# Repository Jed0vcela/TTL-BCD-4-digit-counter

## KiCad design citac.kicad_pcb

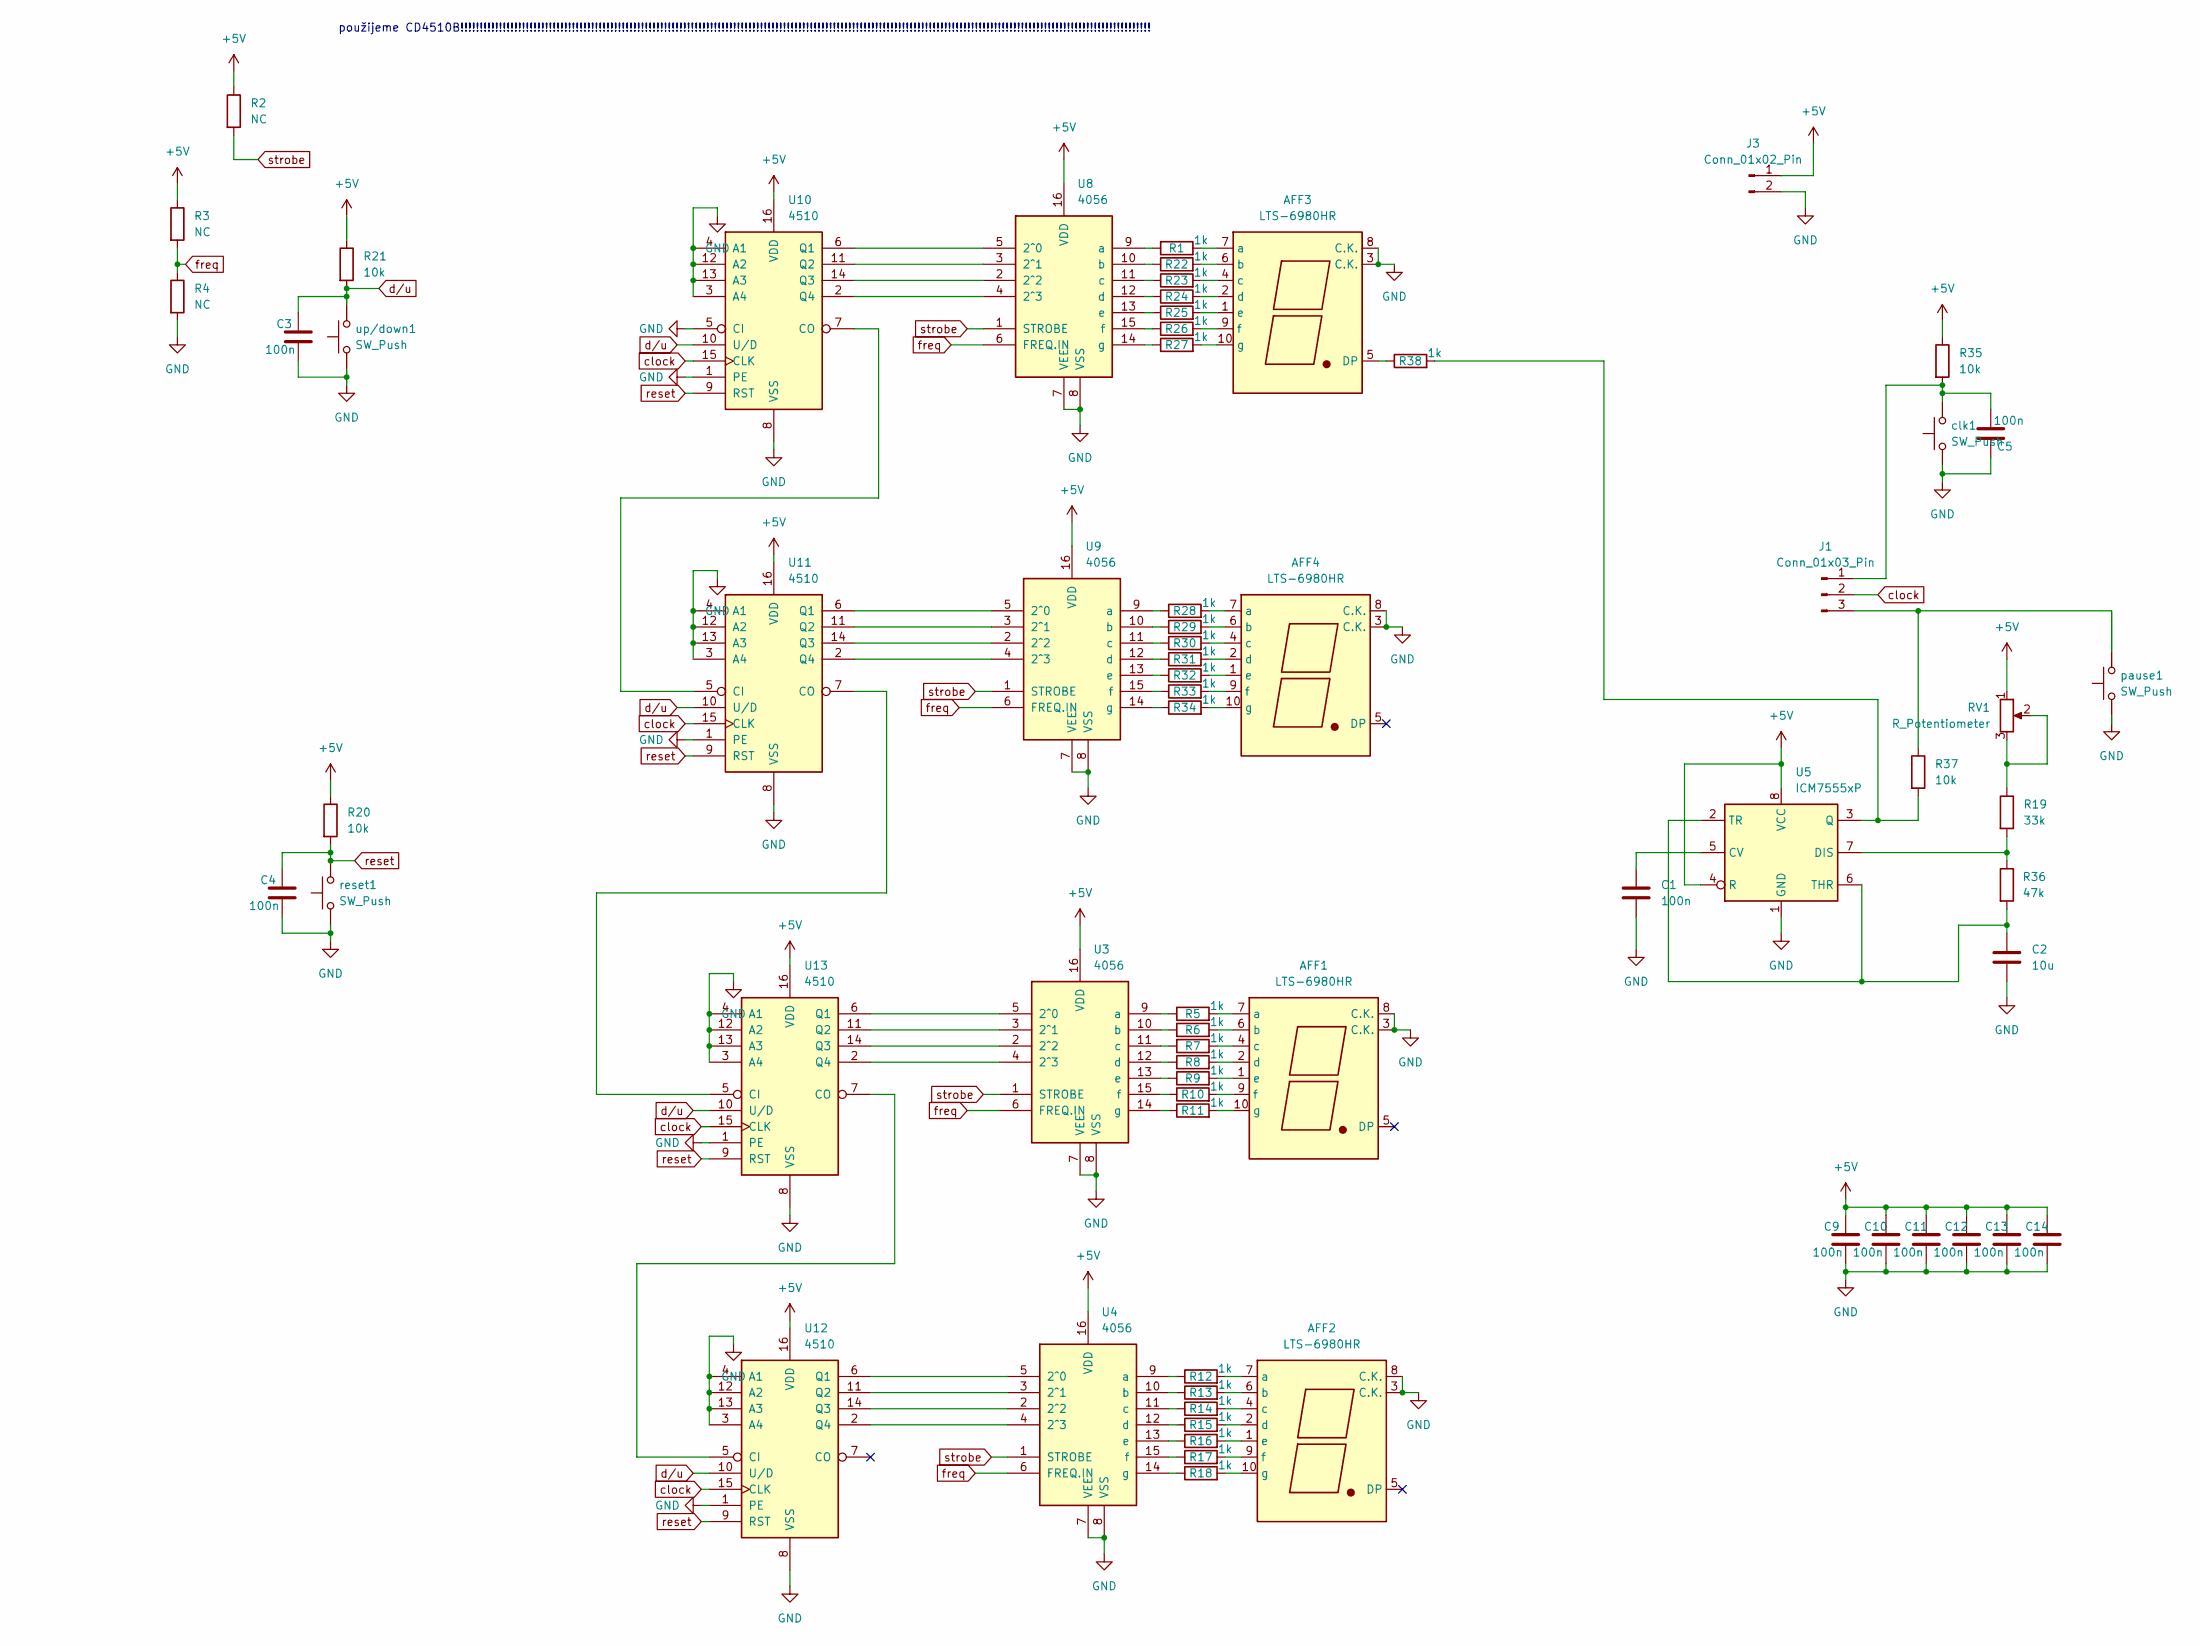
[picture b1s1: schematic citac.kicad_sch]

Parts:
AFF1, AFF2, AFF3, AFF4: LTS-6980HR; 7SegmentLED_LTS6760_LTS6780
C1, C3, C4, C5, C9, C10, C11, C12, C13, C14: 100n; C_1206_3216Metric
C2: 10u; C_1206_3216Metric
J1: Conn_01x03_Pin; PinHeader_1x03_P2.54mm_Vertical
J3: Conn_01x02_Pin; JST_EH_S2B-EH_1x02_P2.50mm_Horizontal
R1, R5, R6, R7, R8, R9, R10, R11, R12, R13, R14, R15, R16, R17, R18, R22, R23, R24, R25, R26, R27, R28, R29, R30, R31, R32, R33, R34, R38: 1k; R_Axial_DIN0207_L6.3mm_D2.5mm_P10.16mm_Horizontal
R2, R3, R4: NC; R_Axial_DIN0207_L6.3mm_D2.5mm_P10.16mm_Horizontal
R19: 33k; R_Axial_DIN0207_L6.3mm_D2.5mm_P10.16mm_Horizontal
R20, R21, R35, R37: 10k; R_Axial_DIN0207_L6.3mm_D2.5mm_P10.16mm_Horizontal
R36: 47k; R_Axial_DIN0207_L6.3mm_D2.5mm_P10.16mm_Horizontal
RV1: R_Potentiometer; Potentiometer_ACP_CA9-V10_Vertical_Hole
U3, U4, U8, U9: 4056; DIP-16_W7.62mm
U5: ICM7555xP; DIP-8_W7.62mm_Socket_LongPads
U10, U11, U12, U13: 4510; DIP-16_W7.62mm_LongPads
clk1: SW_Push; SW_PUSH_6mm
pause1: SW_Push; SW_PUSH_6mm
reset1: SW_Push; SW_PUSH_6mm
up/down1: SW_Push; SW_PUSH_6mm

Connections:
+5V: C9.1, C10.1, C11.1, C12.1, C13.1, C14.1, J3.1, R2.1, R3.1, R20.1, R21.1, R35.1, RV1.1, U3.16 (VDD), U4.16 (VDD), U5.4 (R), U5.8 (VCC), U8.16 (VDD), U9.16 (VDD), U10.16 (VDD), U11.16 (VDD), U12.16 (VDD), U13.16 (VDD)
GND: AFF1.3 (C.K.), AFF1.8 (C.K.), AFF2.3 (C.K.), AFF2.8 (C.K.), AFF3.3 (C.K.), AFF3.8 (C.K.), AFF4.3 (C.K.), AFF4.8 (C.K.), C1.2, C2.2, C3.2, C4.2, C5.1, C9.2, C10.2, C11.2, C12.2, C13.2, C14.2, J3.2, R4.2, U3.7 (VEE), U3.8 (VSS), U4.7 (VEE), U4.8 (VSS), U5.1 (GND), U8.7 (VEE), U8.8 (VSS), U9.7 (VEE), U9.8 (VSS), U10.1 (PE), U10.3 (A4), U10.4 (A1), U10.5 (CI), U10.8 (VSS), U10.12 (A2), U10.13 (A3), U11.1 (PE), U11.3 (A4), U11.4 (A1), U11.8 (VSS), U11.12 (A2), U11.13 (A3), U12.1 (PE), U12.3 (A4), U12.4 (A1), U12.8 (VSS), U12.12 (A2), U12.13 (A3), U13.1 (PE), U13.3 (A4), U13.4 (A1), U13.8 (VSS), U13.12 (A2), U13.13 (A3), clk1.1, pause1.1, reset1.1, up/down1.1
unnamed: AFF1.7 (a), R5.2
unnamed: AFF1.6 (b), R6.2
unnamed: AFF1.4 (c), R7.2
unnamed: AFF1.2 (d), R8.2
unnamed: AFF1.1 (e), R9.2
unnamed: AFF1.9 (f), R10.2
unnamed: AFF1.10 (g), R11.2
unnamed: AFF2.7 (a), R12.2
unnamed: AFF2.6 (b), R13.2
unnamed: AFF2.4 (c), R14.2
unnamed: AFF2.2 (d), R15.2
unnamed: AFF2.1 (e), R16.2
unnamed: AFF2.9 (f), R17.2
unnamed: AFF2.10 (g), R18.2
unnamed: AFF3.5 (DP), R38.1
unnamed: AFF3.7 (a), R1.2
unnamed: AFF3.6 (b), R22.2
unnamed: AFF3.4 (c), R23.2
unnamed: AFF3.2 (d), R24.2
unnamed: AFF3.1 (e), R25.2
unnamed: AFF3.9 (f), R26.2
unnamed: AFF3.10 (g), R27.2
unnamed: AFF4.7 (a), R28.2
unnamed: AFF4.6 (b), R29.2
unnamed: AFF4.4 (c), R30.2
unnamed: AFF4.2 (d), R31.2
unnamed: AFF4.1 (e), R32.2
unnamed: AFF4.9 (f), R33.2
unnamed: AFF4.10 (g), R34.2
unnamed: C5.2, J1.1, R35.2, clk1.2
unnamed: J1.3, R37.1, pause1.2
unnamed: R19.1, RV1.2, RV1.3
unnamed: R5.1, U3.9 (a)
unnamed: R6.1, U3.10 (b)
unnamed: R7.1, U3.11 (c)
unnamed: R8.1, U3.12 (d)
unnamed: R9.1, U3.13 (e)
unnamed: R10.1, U3.15 (f)
unnamed: R11.1, U3.14 (g)
unnamed: R12.1, U4.9 (a)
unnamed: R13.1, U4.10 (b)
unnamed: R14.1, U4.11 (c)
unnamed: R15.1, U4.12 (d)
unnamed: R16.1, U4.13 (e)
unnamed: R17.1, U4.15 (f)
unnamed: R18.1, U4.14 (g)
unnamed: C1.1, U5.5 (CV)
unnamed: R19.2, R36.1, U5.7 (DIS)
unnamed: R37.2, R38.2, U5.3 (Q)
unnamed: C2.1, R36.2, U5.2 (TR), U5.6 (THR)
unnamed: R1.1, U8.9 (a)
unnamed: R22.1, U8.10 (b)
unnamed: R23.1, U8.11 (c)
unnamed: R24.1, U8.12 (d)
unnamed: R25.1, U8.13 (e)
unnamed: R26.1, U8.15 (f)
unnamed: R27.1, U8.14 (g)
unnamed: R28.1, U9.9 (a)
unnamed: R29.1, U9.10 (b)
unnamed: R30.1, U9.11 (c)
unnamed: R31.1, U9.12 (d)
unnamed: R32.1, U9.13 (e)
unnamed: R33.1, U9.15 (f)
unnamed: R34.1, U9.14 (g)
unnamed: U10.7 (CO), U11.5 (CI)
unnamed: U8.5 (2^0), U10.6 (Q1)
unnamed: U8.3 (2^1), U10.11 (Q2)
unnamed: U8.2 (2^2), U10.14 (Q3)
unnamed: U8.4 (2^3), U10.2 (Q4)
unnamed: U11.7 (CO), U13.5 (CI)
unnamed: U9.5 (2^0), U11.6 (Q1)
unnamed: U9.3 (2^1), U11.11 (Q2)
unnamed: U9.2 (2^2), U11.14 (Q3)
unnamed: U9.4 (2^3), U11.2 (Q4)
unnamed: U12.5 (CI), U13.7 (CO)
unnamed: U4.5 (2^0), U12.6 (Q1)
unnamed: U4.3 (2^1), U12.11 (Q2)
unnamed: U4.2 (2^2), U12.14 (Q3)
unnamed: U4.4 (2^3), U12.2 (Q4)
unnamed: U3.5 (2^0), U13.6 (Q1)
unnamed: U3.3 (2^1), U13.11 (Q2)
unnamed: U3.2 (2^2), U13.14 (Q3)
unnamed: U3.4 (2^3), U13.2 (Q4)
clock: J1.2, U10.15 (CLK), U11.15 (CLK), U12.15 (CLK), U13.15 (CLK)
d/u: C3.1, R21.2, U10.10 (U/D), U11.10 (U/D), U12.10 (U/D), U13.10 (U/D), up/down1.2
freq: R3.2, R4.1, U3.6 (FREQ.IN), U4.6 (FREQ.IN), U8.6 (FREQ.IN), U9.6 (FREQ.IN)
reset: C4.1, R20.2, U10.9 (RST), U11.9 (RST), U12.9 (RST), U13.9 (RST), reset1.2
strobe: R2.2, U3.1 (STROBE), U4.1 (STROBE), U8.1 (STROBE), U9.1 (STROBE)

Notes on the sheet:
použijeme CD4510B!!!!!!!!!!!!!!!!!!!!!!!!!!!!!!!!!!!!!!!!!!!!!!!!!!!!!!!!!!!!!!!!!!!!!!!!!!!!!!!!!!!!!!!!!!!!!!!!!!!!!!!!!!!!!!!!!!!!!!!!!!!!!!!!!!!!!!!!!!!!!!!!!!!!!!!!!!!!!!!!!!!!!!!!!!!!!!!!!!!!

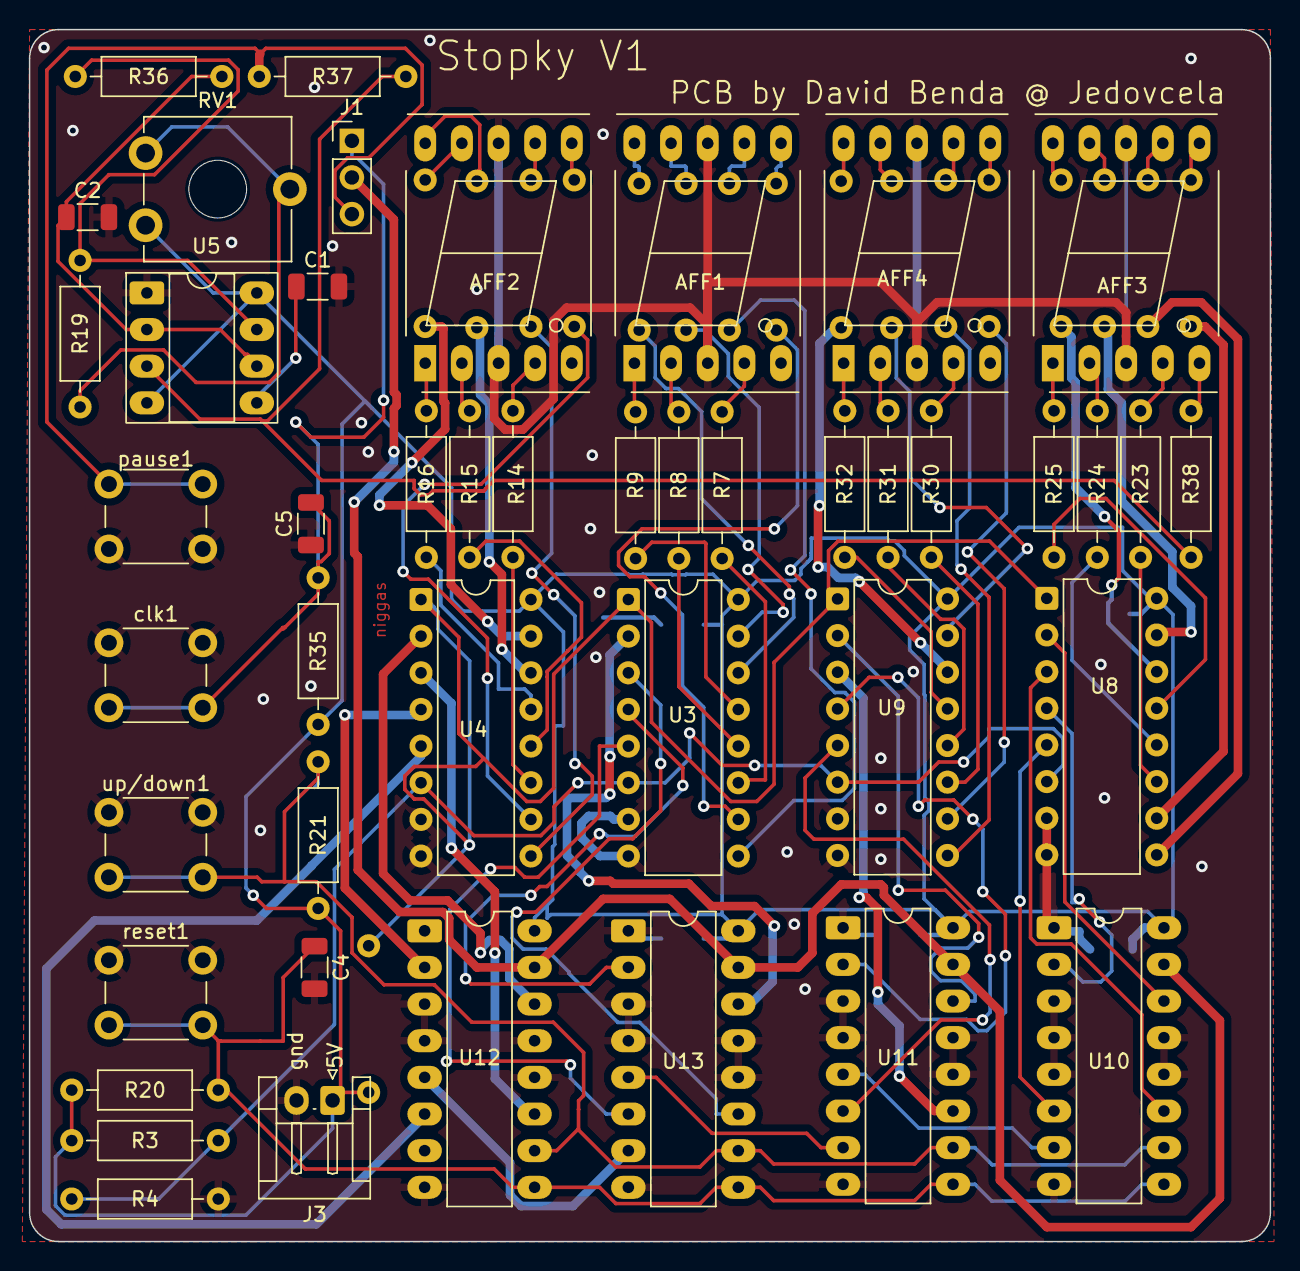
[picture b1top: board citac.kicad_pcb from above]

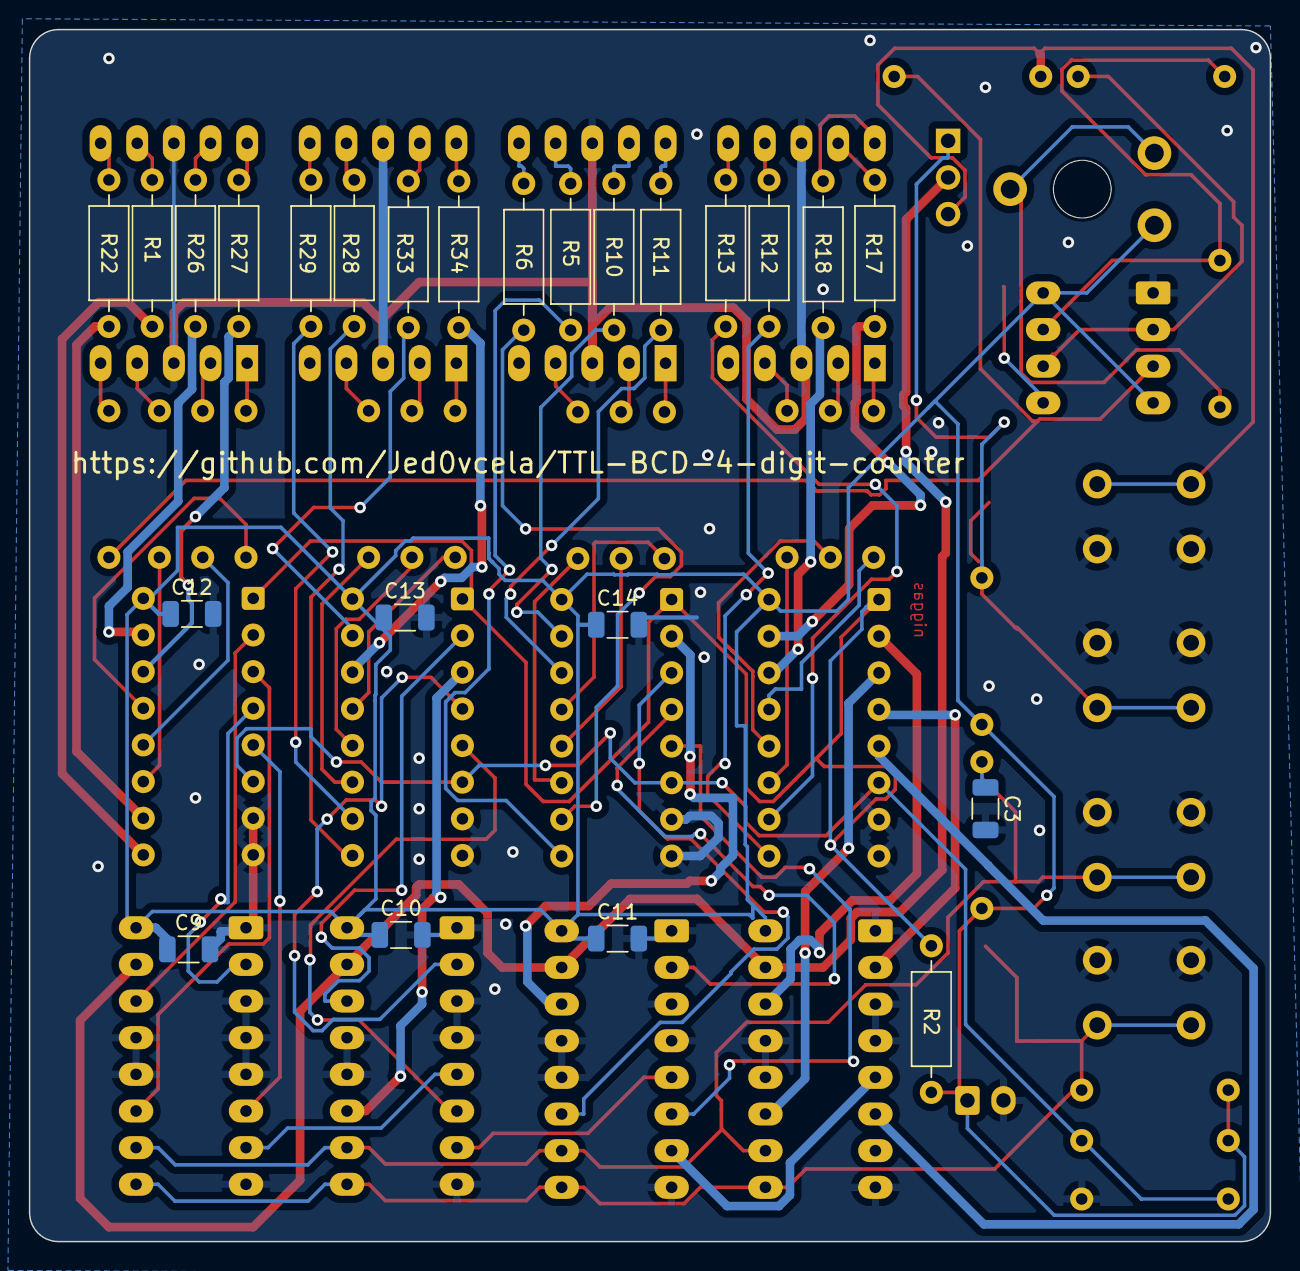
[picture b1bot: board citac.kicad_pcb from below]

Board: 2 copper layers, 86.0 x 84.0 mm, 69 parts (24 on the bottom side), 90 nets.

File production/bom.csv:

Designator,Footprint,Quantity,Value,LCSC Part #
"AFF1, AFF2, AFF3, AFF4",7SegmentLED_LTS6760_LTS6780,4,LTS-6980HR,
"C1, C10, C11, C12, C13, C14, C3, C4, C5, C9",1206,10,100n,
C2,1206,1,10u,
"CLK1, PAUSE1, RESET1, UP/DOWN1",SW_PUSH_6mm,4,SW_Push,
J1,PinHeader_1x03_P2.54mm_Vertical,1,Conn_01x03_Pin,
J3,JST_EH_S2B-EH_1x02_P2.50mm_Horizontal,1,Conn_01x02_Pin,
"R1, R10, R11, R12, R13, R14, R15, R16, R17, R18, R22, R23, R24, R25, R26, R27, R28, R29, R30, R31, R32, R33, R34, R38, R5, R6, R7, R8, R9",R_Axial_DIN0207_L6.3mm_D2.5mm_P10.16mm_Horizontal,29,1k,
R19,R_Axial_DIN0207_L6.3mm_D2.5mm_P10.16mm_Horizontal,1,33k,
"R2, R3, R4",R_Axial_DIN0207_L6.3mm_D2.5mm_P10.16mm_Horizontal,3,NC,
"R20, R21, R35, R37",R_Axial_DIN0207_L6.3mm_D2.5mm_P10.16mm_Horizontal,4,10k,
R36,R_Axial_DIN0207_L6.3mm_D2.5mm_P10.16mm_Horizontal,1,47k,
RV1,Potentiometer_ACP_CA9-V10_Vertical_Hole,1,R_Potentiometer,
"U10, U11, U12, U13",DIP-16_W7.62mm_LongPads,4,4510,
"U3, U4, U8, U9",DIP-16_W7.62mm,4,4056,
U5,DIP-8_W7.62mm_Socket_LongPads,1,ICM7555xP,

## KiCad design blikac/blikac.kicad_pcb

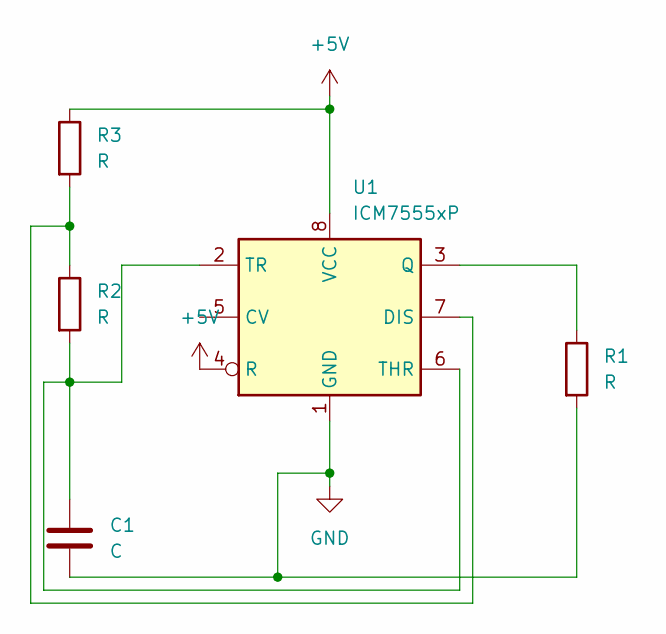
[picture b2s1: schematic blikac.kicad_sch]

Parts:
C1: C; C_1206_3216Metric
R1, R2, R3: R; R_Axial_DIN0309_L9.0mm_D3.2mm_P12.70mm_Horizontal
U1: ICM7555xP; SOIC-8_3.9x4.9mm_P1.27mm

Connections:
+5V: R3.1, U1.4 (R), U1.8 (VCC)
GND: C1.2, R1.2, U1.1 (GND)
unnamed: R2.1, R3.2, U1.7 (DIS)
unnamed: R1.1, U1.3 (Q)
unnamed: C1.1, R2.2, U1.2 (TR), U1.6 (THR)

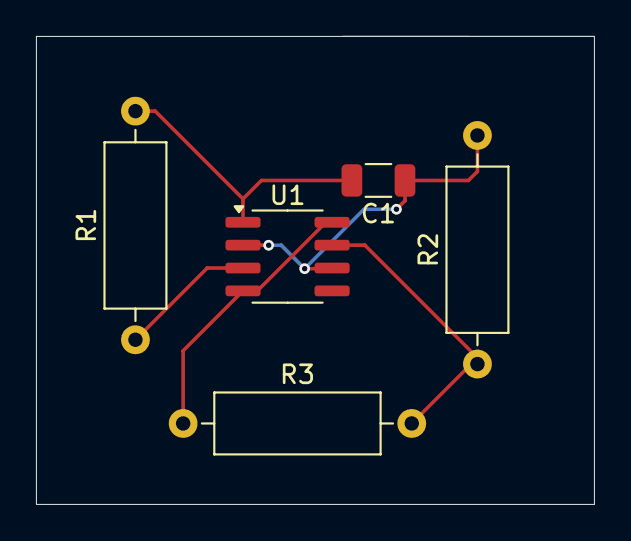
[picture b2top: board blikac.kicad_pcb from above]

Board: 2 copper layers, 31.0 x 26.0 mm, 5 parts (0 on the bottom side), 5 nets.

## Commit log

2025-05-12 upload
